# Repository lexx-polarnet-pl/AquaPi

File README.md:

# AquaPi

The aim of this project is to build Raspberry Pi controlled platform for aquarium management.

## Table of contents
* [General info](#general-info)
* [Screenshots](#screenshots)
* [Versions](#Versions)
* [Setup](#setup)
* [Features](#features)
* [Status](#status)
* [Inspiration](#inspiration)
* [Contact](#contact)

## General info
This project is licensed using GPL 2.0 version.
It's combination of hardware layer and software as well.
Structure of directories is following:

* Software - source codes of daemon and php web ui.
* Hardware - all hardware designs (created using KiCad).
* Doc      - place for documentation.

You can like it or not, but software is written (and documentation as well) in Polish language.

## Screenshots

## Versions
* Version 1.0 - still one and only stable version that was released.
* Version 2.0 - aka still in development phase - far more advanced than previous one, but also still not finished (but quite stable).

## Setup
Please see Doc directory if you wish to learn more about setup process.

## Features
List of features ready:
* Heating/cooling tank with different temperature settings between night and day.
* Light control with PWM usage to simulate sunrise/dawn.
* Recording of statistical data collected from sensors into database, and visualization on charts.
* Can be controlled using web browser, both on PC and mobile phone.
* Outputs controlled with timers with 1 second accuracy (nice for DIY feeders or fertilizers).

TODOs for future development:
* still some stuff to do with CO&#8322;.
* and probably more small staff to do.

## Status
Project is: in progress.

## Inspiration
This project was inspired by [Aquamat](https://github.com/musashimm/aquamat). 

## Contact
Created by [lexx](mailto:lexx@polarnet.pl) (https://lexx.polarnet.pl/) - feel free to contact me!
AquaPi is also having its own home page - see https://aquapi.polarnet.pl/

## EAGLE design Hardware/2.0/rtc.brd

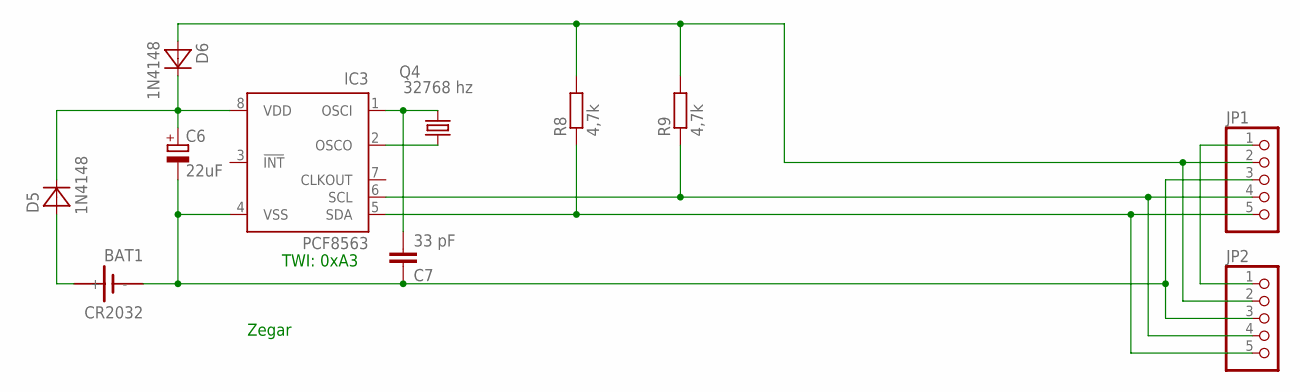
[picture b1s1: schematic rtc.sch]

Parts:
BAT1: CR2032; SN2932_LISPOL
C6: 22uF; E2,5-5
C7: 33 pF; C050-024X044
D5, D6: 1N4148; DO35-7
IC3: PCF8563; DIL08
JP1, JP2: PINHD-1X5/90; 1X05/90
Q4: 32768 hz; TC26V
R8, R9: 4,7k; R1206

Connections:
+5V: D6.A, JP1.2, JP2.2, R8.2, R9.2
+12V: JP1.1, JP2.1
GND: BAT1.-, C6.-, C7.1, IC3.4 (VSS), JP1.3, JP2.3
unnamed: IC3.2 (OSCO), Q4.1
unnamed: C7.2, IC3.1 (OSCI), Q4.2
unnamed: C6.+, D5.C, D6.C, IC3.8 (VDD)
unnamed: BAT1.+, D5.A
SCL: IC3.6 (SCL), JP1.4, JP2.4, R9.1
SDA: IC3.5 (SDA), JP1.5, JP2.5, R8.1

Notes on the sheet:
TWI: 0xA3
Zegar

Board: 2 copper layers, 11 parts (3 on the bottom side), 9 nets, no tracks yet.

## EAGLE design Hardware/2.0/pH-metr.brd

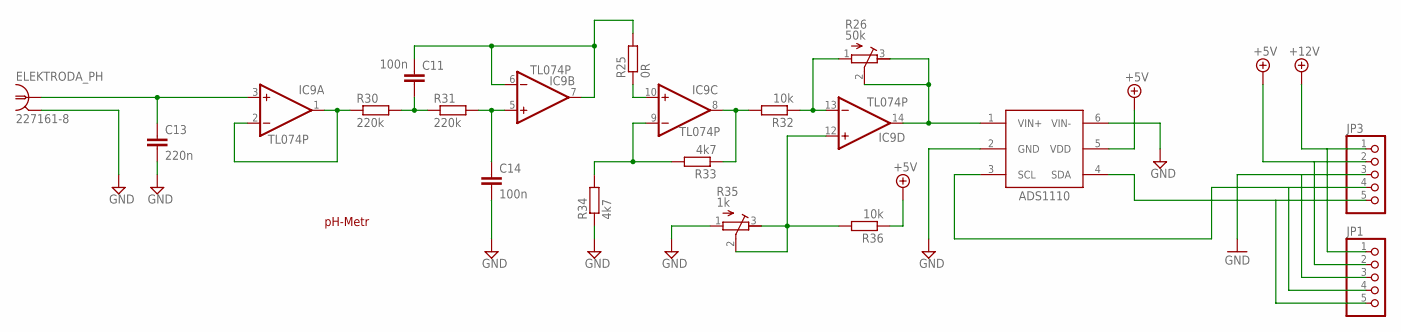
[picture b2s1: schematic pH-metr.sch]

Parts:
C11, C14: 100n; C1206
C13: 220n; C050-025X075
ELEKTRODA_PH: 227161-8; AMP_227161
IC2: ADS1110; SOT-23-6
IC9: TL074P; DIL14
JP1, JP3: PINHD-1X5/90; 1X05/90
R25: 0R; R1206
R26: 50k; RTRIM64X
R30, R31: 220k; R1206
R32, R36: 10k; R1206
R33, R34: 4k7; R1206
R35: 1k; RTRIM64X

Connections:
+5V: IC2.5 (VDD), JP1.2, JP3.2, R36.1
+12V: JP1.1, JP3.1
GND: C13.2, C14.2, ELEKTRODA_PH.2 (GND), IC2.2 (GND), IC2.6 (VIN-), JP1.3, JP3.3, R34.1, R35.1 (A)
unnamed: C13.1, ELEKTRODA_PH.1, IC9.3 (+IN)
unnamed: IC9.12 (+IN), R35.2 (S), R35.3 (E), R36.2
unnamed: IC9.10 (+IN), R25.1
unnamed: IC9.13 (-IN), R26.1 (A), R32.1
unnamed: IC9.1 (OUT), IC9.2 (-IN), R30.1
unnamed: C11.2, R30.2, R31.1
unnamed: C14.1, IC9.5 (+IN), R31.2
unnamed: C11.1, IC9.6 (-IN), IC9.7 (OUT), R25.2
unnamed: IC9.9 (-IN), R33.2, R34.2
unnamed: IC9.8 (OUT), R32.2, R33.1
PHOUT: IC2.1 (VIN+), IC9.14 (OUT), R26.2 (S), R26.3 (E)
SCL: IC2.3 (SCL), JP1.4, JP3.4
SDA: IC2.4 (SDA), JP1.5, JP3.5
V+: IC9.4 (V+)
V-: IC9.11 (V-)

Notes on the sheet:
pH-Metr

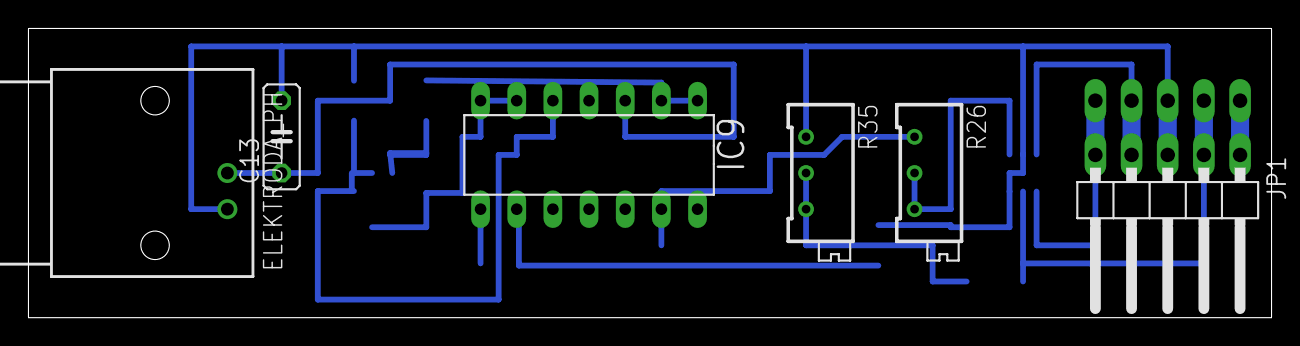
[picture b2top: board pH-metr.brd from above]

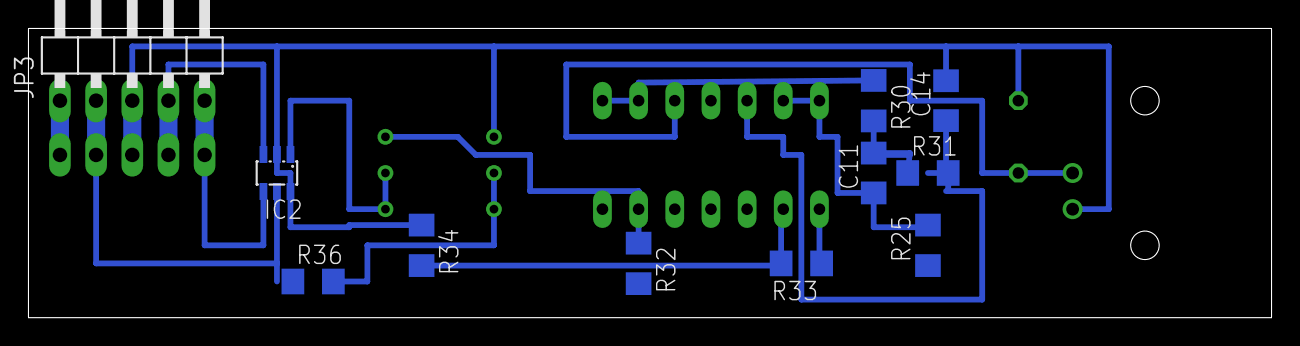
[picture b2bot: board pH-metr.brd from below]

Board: 2 copper layers, 87.3 x 20.3 mm, 17 parts (11 on the bottom side), 16 nets.

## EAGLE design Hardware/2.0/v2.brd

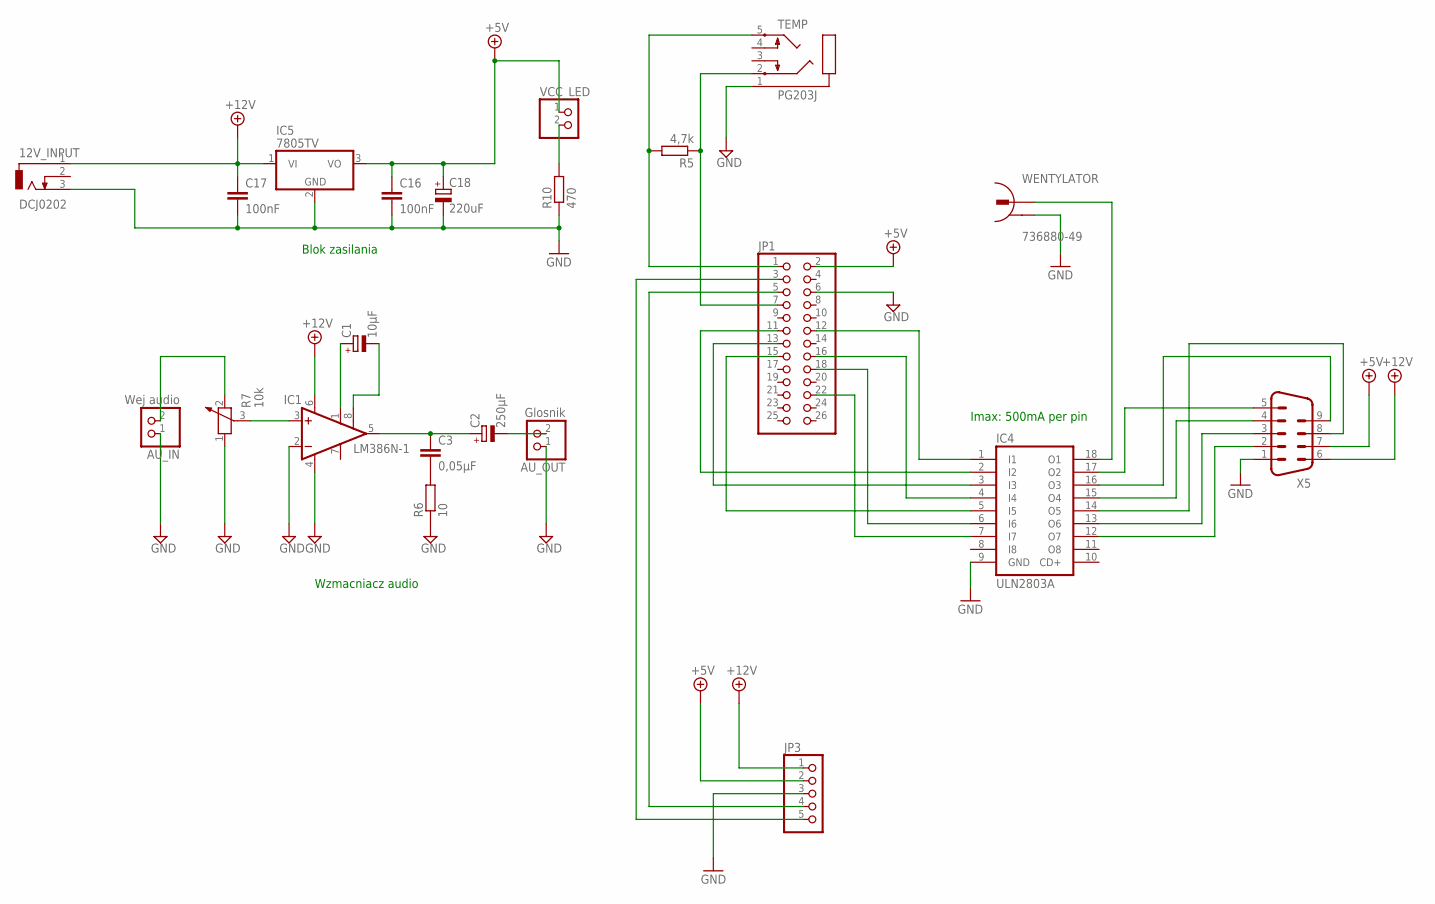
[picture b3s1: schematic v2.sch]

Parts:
12V_INPUT: DCJ0202
AU_IN: Wej audio; 1X02
AU_OUT: Glosnik; 1X02
C1: 10µF; E2,5-5
C2: 250µF; E2,5-6
C3: 0,05µF; C025-024X044
C16, C17: 100nF; C050-024X044
C18: 220uF; E2,5-5
IC1: LM386N-1; DIL08
IC4: ULN2803A; DIL18
IC5: 7805TV; TO220V
JP1: PINHD-2X13; 2X13
JP3: PINHD-1X5/90; 1X05/90
R5: 4,7k; R1206
R6: 10; R1206
R7: 10k; PT-10
R10: 470; R1206
TEMP: PG203J
VCC_LED: PINHD-1X2; 1X02
WENTYLATOR: 736880-49
X5: M09H

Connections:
+5V: C16.1, C18.+, IC5.3 (VO), JP1.2, JP3.2, VCC_LED.1, X5.7
+12V: 12V_INPUT.1, C17.1, IC1.6 (VS), IC5.1 (VI), JP3.1, X5.6
GND: 12V_INPUT.3, AU_IN.1, AU_OUT.1, C16.2, C17.2, C18.-, IC1.2 (-IN), IC1.4 (GND), IC4.9 (GND), IC5.2 (GND), JP1.6, JP3.3, R6.1, R7.1, R10.1, TEMP.1, WENTYLATOR.2, X5.1
unnamed: IC4.3 (I3), JP1.13
unnamed: IC4.4 (I4), JP1.16
unnamed: IC4.1 (I1), JP1.12
unnamed: IC4.13 (O6), X5.3
unnamed: IC4.16 (O3), X5.9
unnamed: IC4.12 (O7), X5.2
unnamed: IC4.7 (I7), JP1.22
unnamed: IC4.5 (I5), JP1.15
unnamed: IC4.14 (O5), X5.8
unnamed: IC4.6 (I6), JP1.18
unnamed: JP1.1, R5.2, TEMP.5
unnamed: JP1.7, R5.1, TEMP.2
unnamed: IC4.17 (O2), X5.5
unnamed: R10.2, VCC_LED.2
unnamed: IC4.18 (O1), WENTYLATOR.1
unnamed: C1.+, IC1.1 (GAIN)
unnamed: IC4.15 (O4), X5.4
unnamed: IC4.2 (I2), JP1.11
unnamed: C1.-, IC1.8 (GAIN)
unnamed: C2.+, C3.1, IC1.5 (OUT)
unnamed: AU_OUT.2, C2.-
unnamed: C3.2, R6.2
unnamed: IC1.3 (+IN), R7.3
unnamed: AU_IN.2, R7.2
SCL: JP1.5, JP3.4
SDA: JP1.3, JP3.5

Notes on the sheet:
Wzmacniacz audio
Blok zasilania
Imax: 500mA per pin

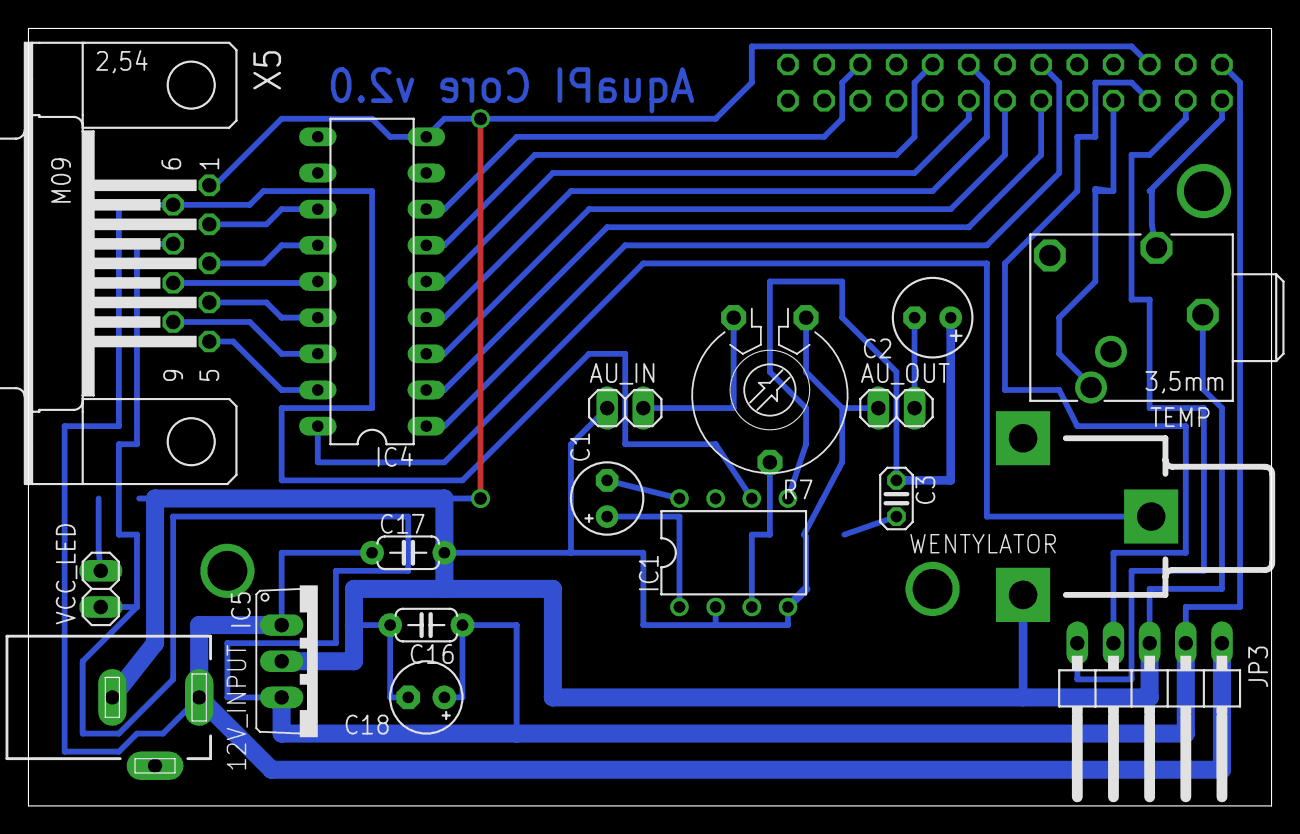
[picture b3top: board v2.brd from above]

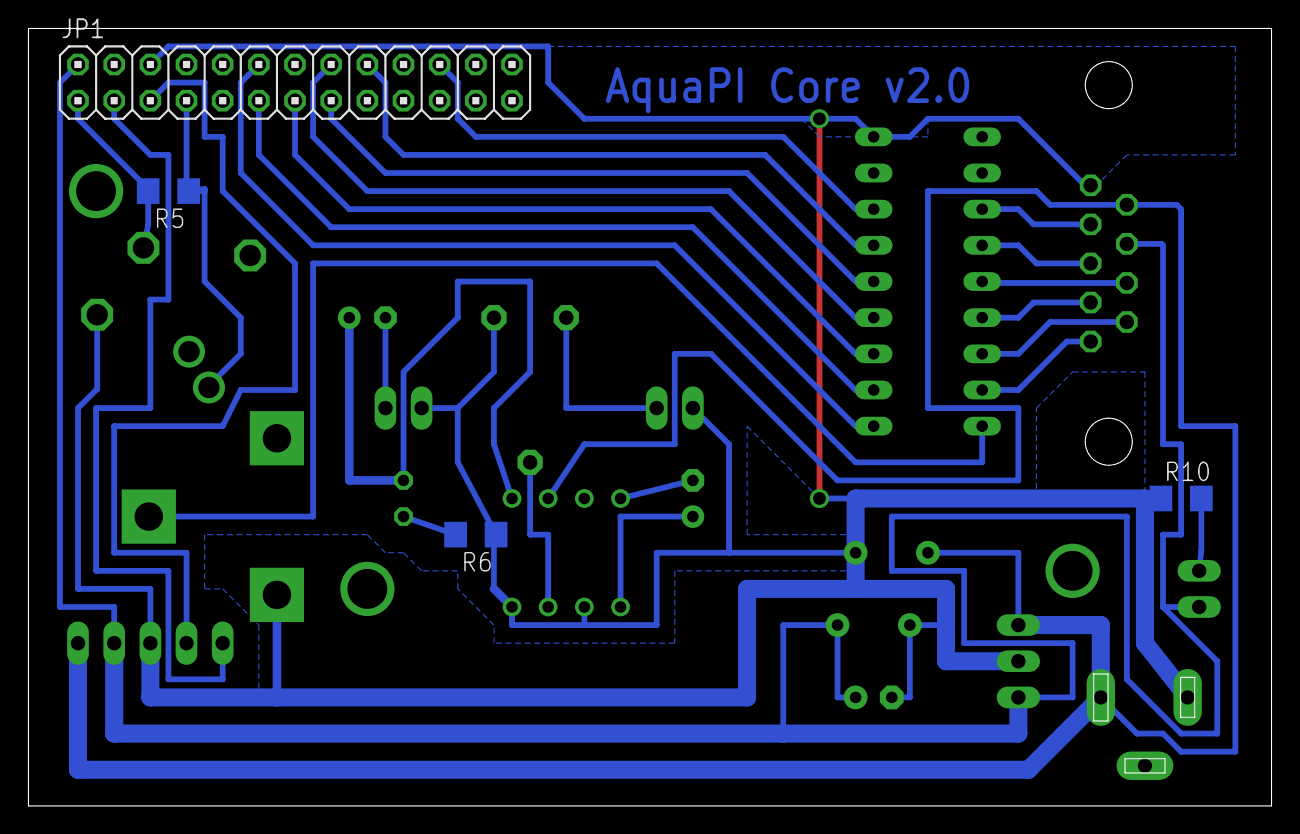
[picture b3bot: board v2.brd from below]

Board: 2 copper layers, 87.3 x 54.6 mm, 22 parts (4 on the bottom side), 29 nets.

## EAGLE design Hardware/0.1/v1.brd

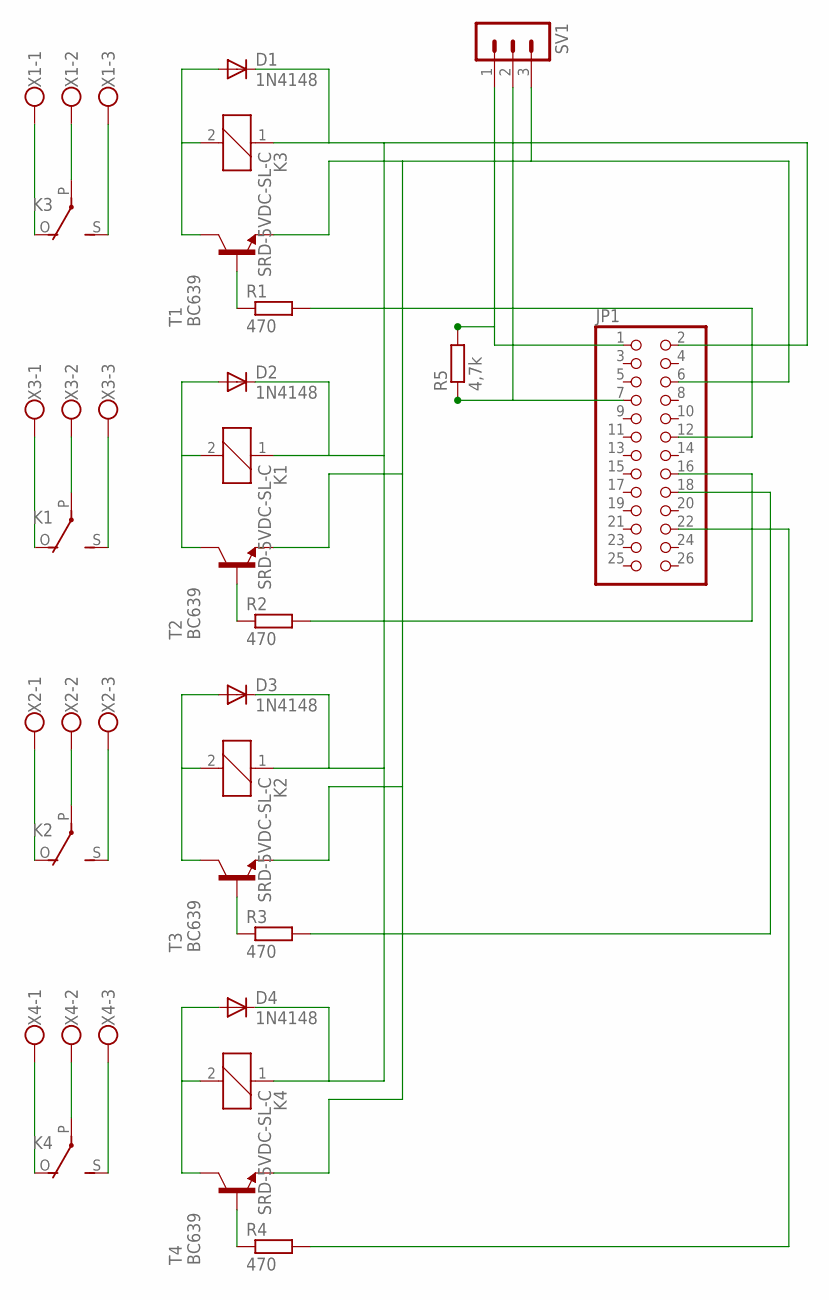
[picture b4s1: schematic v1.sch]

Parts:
D1, D2, D3, D4: 1N4148; DO41-10
JP1: PINHD-2X13; 2X13
K1, K2, K3, K4: SRD-5VDC-SL-C; ZF112
R1, R2, R3, R4: 470; 0204/7
R5: 4,7k; 0207/7
SV1: MA03-1
T1, T2, T3, T4: BC639; TO92-ECB
X1, X2, X3, X4: W237-103

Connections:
unnamed: JP1.12, R1.2
unnamed: D1.A, K3.2, T1.C
unnamed: JP1.16, R2.2
unnamed: JP1.6, SV1.3, T1.E, T2.E, T3.E, T4.E
unnamed: R1.1, T1.B
unnamed: K3.P, X1.2
unnamed: K3.S, X1.3
unnamed: K3.O, X1.1
unnamed: D1.C, D2.C, D3.C, D4.C, JP1.2, K1.1, K2.1, K3.1, K4.1
unnamed: D2.A, K1.2, T2.C
unnamed: JP1.1, R5.2, SV1.1
unnamed: R2.1, T2.B
unnamed: D3.A, K2.2, T3.C
unnamed: K1.P, X3.2
unnamed: K1.S, X3.3
unnamed: K1.O, X3.1
unnamed: R3.1, T3.B
unnamed: JP1.7, R5.1, SV1.2
unnamed: K2.P, X2.2
unnamed: K2.S, X2.3
unnamed: K2.O, X2.1
unnamed: JP1.18, R3.2
unnamed: D4.A, K4.2, T4.C
unnamed: R4.1, T4.B
unnamed: K4.P, X4.2
unnamed: K4.S, X4.3
unnamed: K4.O, X4.1
unnamed: JP1.22, R4.2

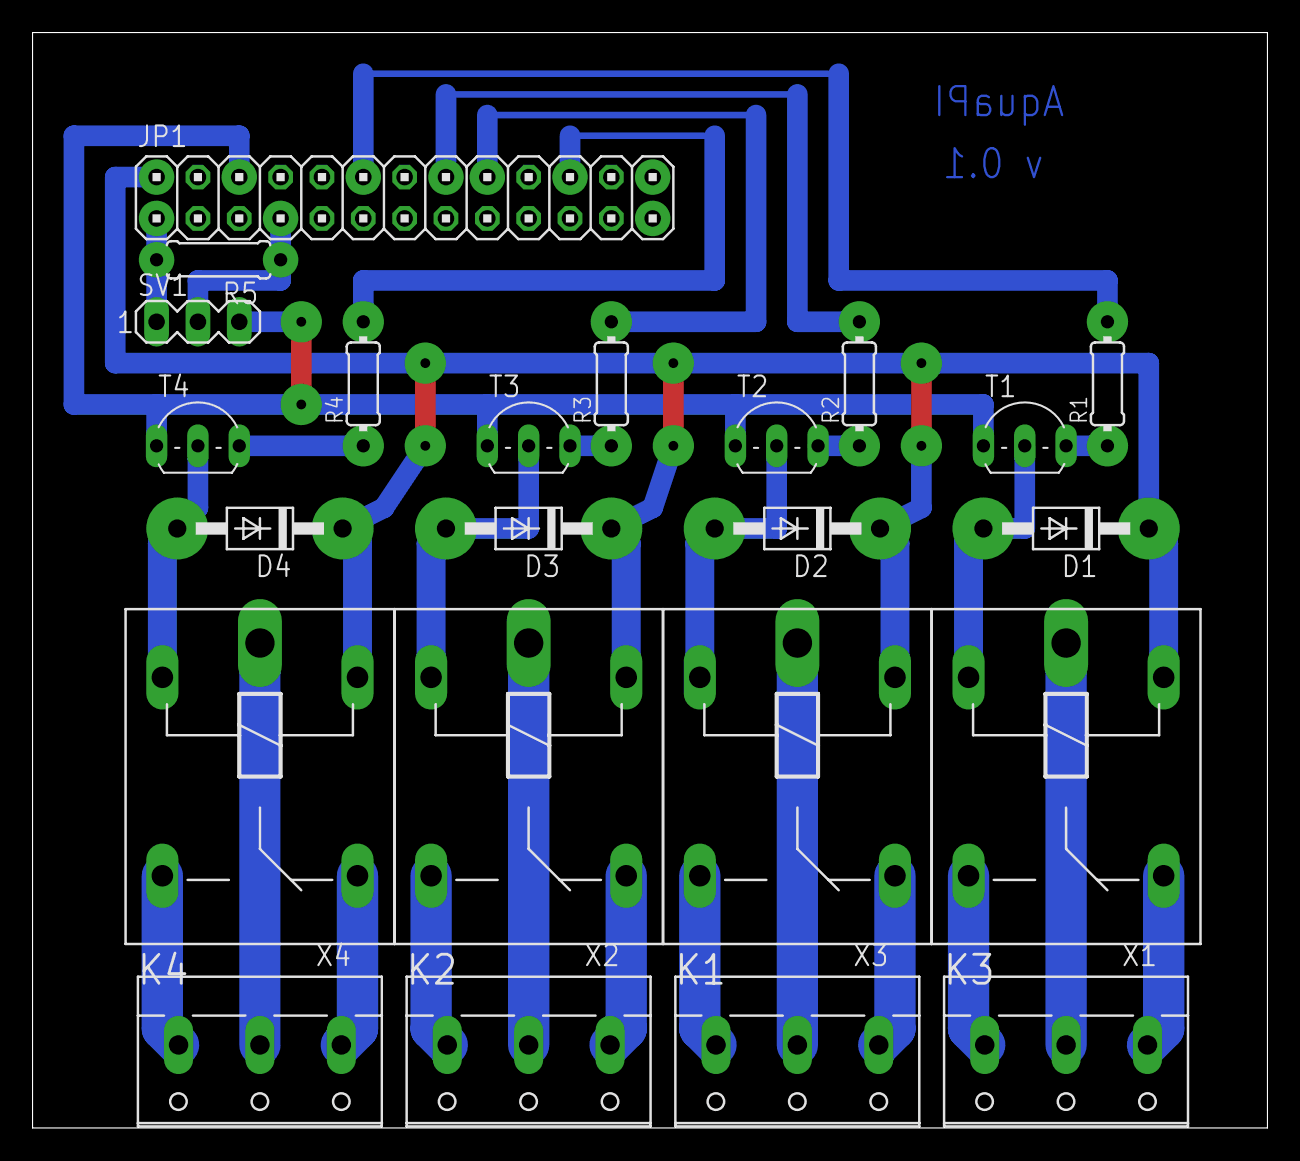
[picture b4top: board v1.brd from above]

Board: 2 copper layers, 75.9 x 67.3 mm, 23 parts (0 on the bottom side), 28 nets.

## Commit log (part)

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2013-11-11 poprawka warunku
2013-11-11 opis
2013-11-11 dostosowanie do nowej klasy DB
2013-11-11 zgodność ze starszą wersja PHP
2013-11-11 mozliwosc nie wyświetlania czujników na wykresie
2013-11-11 implementacja IPC
2013-11-11 Wczytywanie pozostałych parametrów daemona z ini
2013-11-11 poprawki wizualne
2013-11-12 dopasowanie do nowej klasy DB
2013-11-12 Update README.txt
    ort :P
2013-11-13 poprawa formatowania
2013-11-13 dodana lista autorów
2013-11-13 przepis na udaną (prawie) instalację
2013-11-13 fix na pustą baze
2013-11-14 work around na Strict Standards: Only variables should be passed by reference
2013-11-14 poprawka na wypadek braku timerów
2013-11-14 nie mozna było dodac sensora ktory nie miał byc pokazywany na wykresie.
2013-11-14 Update aquapi.sql
    rozszerzenie tabeli sensors
2013-11-14 oznaczanie jednego sensora jako master dla zgodnosci z demonem :(
2013-11-14 zmiana w demonie uwzgledniajaca tabele sensors
2013-11-15 poprawki zwiazane glownie z radzeniem sobie z brakiem danych w bazie
2013-11-15 porządki i zmiana nazewnictwa wyjść
2013-11-15 zapomniany commit
2013-11-16 dodane 2 funkcje pomocnicze
2013-11-16 nowy konfig
2013-11-17 Zaczątki dokumentacji
2013-11-17 przystosowanie strony konfiguracyjnej do nowej bazy + przebudowa
2013-11-18 kolejne poprawki stabilności
2013-11-19 zmiany w dokumentacji
2013-11-19 świerzo wygenerowana dokumentacja
2013-11-19 usunięcie zbędnych fragmentów RelayBoard
2013-11-19 Zmiany w about
2013-11-19 Ujednolicanie WebUi
2013-11-20 sprawdzanie poprawnego odczytu sensorów. błedne odczyty są odrzucane, a zdarzenie logowane
2013-11-20 poprawa drobnych błędów
2013-11-20 poprawki na liczne PHP Notice, poprawka demona, poprawka na brakujący podsystem 1wire.
2013-11-20 memmory leak fix
2013-11-22 2 formatki dodawania timerów.
2013-11-22 poprawka wysypujacego sie demona
2013-11-23 Dodana możliwość zabezpieczenia webui hasłem
2013-11-23 zbędny plik
2013-11-24 demon loguje temperatory z czujnika dummy, poprawka aktualizacji sensorów, temperatury nocne. poprawione duperele.
2013-11-25 ciąg dalszy dokumentacji
2013-11-25 Tu nie jest wymagany
2013-11-25 zmiana
2013-11-26 jeszcze zmiany
2013-11-26 poprawki po merge
2013-12-28 dostosowanie do nowego formatu bazy
2013-12-28 enable $id$ tag
2013-12-29 Podstawowa obsługa timerów (czasowych) jeszcze bez dni tygodnia
2013-12-29 poprawki w UI oraz rozbudowa IPC - statusy urządzeń są teraz czytane bezpośrednio z daemona bez użycia bazy
2013-12-30 konwersja na UTF8
2013-12-30 Raportowanie stanu nieustalonego
2014-01-02 zmiana roku
2014-01-08 Zaczątek obsługi dni tygodnia
2014-01-23 naprawa nie działajacego przełaczania sekcji w ustawieniach
2014-01-24 aktywacja zakładki kamery
2014-01-25 poprawka dashboard o brakujace sekcje. opcja w ini do ich właczania
2014-01-26 Poprawa ustawień czujników, mozliwosc wyłaczenia czujnika, opcja w konfiguracja wskazujaca czy demon jest lokalny czy zdalny, korekta dashboard.
2014-02-02 id + drobne poprawki
2014-02-11 poprawka master sensora
2014-02-13 poprawki czasu, opisów i jakiejs drobnicy.
2014-03-01 Drobna poprawka nagłówka
2014-03-01 Dodany viewport - nie zmniejszaj ekranu na komórkach
2014-03-01 dopiski w dokumentacji
2014-03-01 zwiększenie limitu failcount
2014-03-02 Lekkie poprawki pod urządzenia mobilne, chociaż jeszcze długa droga...
2014-03-02 Eksperyment z layoutem
2014-03-15 poprawka zapisywania nowych sensorów do bazy.
2014-03-15 uruchomienie wykresów. brak wsparcia dla brakujacych danych. (trzeba by generowac null przy wyciaganiu danych)
2014-03-15 poprawka przedrostka dummy
2014-03-15 Update aquapi.c
    literówka
2014-03-15 reload_freq jest obsługiwane
2014-03-15 korekta zapytania
2014-03-16 poprawa wyswietlania logów, czyszczenie logów, nowa opcja w konfigu, zmiana nazwy pliku ini z konfiguracją.
2014-03-16 poprawka na brakujaca opcje aby nie czysciło całych logów
2014-03-16 zmiana ikonek
2014-03-16 Update aquapi.ini
    opcja kamera
2014-03-16 dopasowanie do nowego konfiga
2014-03-16 wyłaczanie kawałków kodu zgodnie z opcjami w ini
2014-03-16 Update tcpip.c
    config.interface => config.host
2014-03-16 Update aquapi.c
    bind-address, bind-port
2014-03-16 Update tcpip.c
    _
2014-03-16 Update aquapi.c
    _
2014-03-16 Update inifile.c
    _
2014-03-16 Update aquapi.ini
    _
2014-03-16 wartości domyślne
2014-03-16 negowanie wyjść
2014-03-16 usunięcie $Id
2014-03-16 dodano xml2array
2014-03-16 Delete aquapi2.ini
    nie potrzebny
2014-03-16 dopasowanie ustawien do ipc->1wlist
2014-03-16 ustandaryzowanie nazwy templatki
2014-03-16 kolorowanie i lepsze opisy dla devel
2014-03-16 fix, ale brzydki
2014-03-17 mozliwosc usuniecia czujników dummy
2014-03-17 poprawka wizualna
2014-03-17 Usunięcie zbędnych $Id$
2014-03-18 lepsza obsługa rb
2014-03-18 usuniecie usera
2014-03-18 usunięcie usera
2014-03-18 obsługa czujników systemowych
2014-03-18 aktualizacja struktury DB
2014-03-18 cleanup i dodanie komendy aquapi:sysinfo
2014-03-18 poprawki
2014-03-19 poprawki konfiguracji gpio, zmina zrodla danych dashboarda
2014-03-19 Dodanie obsługi korekty temp. nocnej
2014-03-19 zapis stanu wyjść
2014-03-19 usunięte już zrobione
2014-03-19 kolejne zrobione
2014-03-19 Wycięcie warningów
2014-03-20 wartości nieokreślone z czujników są zapisywane w bazie jako null
2014-03-21 obsługa wyłaczonych czujników + opis typów wejsc RB
2014-03-21 przeróbka dashboard
2014-03-21 dodana obsługa taga <NOBR></NOBR>
2014-03-22 wykresy przekaźników, wyłaczanie przekaźników w konfiguracji, rożne drobne poprawki.
2014-03-22 porawka tytułu
2014-03-22 fix tabeli
2014-03-22 poprawka Jarka
2014-03-22 początek obsługi manualnego włączania wyjść w demonie
2014-03-31 dodanie obsługi pseudoczujnika rpi:system:txtfile
2014-03-31 poprawka na odczyt 85stopni z DSa
2014-03-31 plugin odczytujacy pogode :)
2014-04-01 dodane identyfikatory sensorów
2014-04-01 dodanie 2 tabeli
    dodanie tabeli jednostek oraz relacji jednostek z interfejsami
2014-04-01 dodanie konfigurowalnych jednostek dla sensorów
2014-04-05 drobne fixy
2014-04-05 poprawka symbolu jednostki
2014-04-06 przeniesienie pluginów
2014-04-06 plugin weather.php uzywa danych z pliku ini i bazy.
2014-04-06 poprawka pluginu
2014-04-06 https://github.com/lexx-polarnet-pl/AquaPi/issues/21
    sensor głowny wyswietla sie na dashboard
2014-04-06 pwm w UI
2014-04-06 trigery pwm w UI
2014-06-16 Update aquapi.sql
    dodanie nowej tabeli
2014-06-16 zmiana sposobu kasowania
2014-06-29 poprawka zapisywania kalendarza. sekcja ustawienien urzadzenia wyswietla sie na podstawie właczonego/wyłaczonego urzadzenia, a nie na podstawie istnienia interfejsów tego urzadzenia.
2014-06-29 zmiana sposobu prezentacji timestampów
2014-06-29 dodanie kalendarza i jego obsługi
2014-06-29 Update aquapi.sql
    db_version fix
2014-06-30 poprawka na dirty hack
2014-07-01 poprawa zdarzen z kalendarza na dashboardzie
2014-07-02 zapomniany plik z upgradem
2014-07-02 kolorowanie komunikatów z kalendarz, odczyt s/n płyty rpi.
2014-07-02 dodanie opcji właczania i wyłaczania nowych sekcji/pluginów
2014-07-04 mod bazy pod zatwierdzanie zdarzeń
2014-07-04 to też powinno być opcjonalne
2014-07-05 dodany tip
2014-07-05 demon nie powinien się wywalać na systemach innych niż raspi przy próbie użycia GPIO
2014-07-06 na -O3 segfaulci na i386, piwo temu kto mi powie czemu
2014-07-06 zmniejszenie czasu oczekiwania na zmianę stanu interfacu + poprawa obsługi w UI
2014-07-06 poprawka formatu daty na bardziej czytelną
2014-07-07 usunięte zbędne dzielenie
2014-07-07 wizualizacja trybu auto i ręcznego
2014-07-07 Pokazywanie wszystkich wyjść w jednej tabelce
2014-07-08 negowanie
2014-07-08 negowanie było w złym miejscu
2014-07-09 todo jest teraz wissues na githubie
2014-07-13 podejście do tematu jak wyświetlać możliwe do ustawienia wejścia/wyjścia
2014-07-21 nieco inne dodawanie urządzeń
2014-07-22 poprawka na wejścia fully_editable_address (czyli np. plik tekstowy)
2014-08-01 Dodana (wstępna bo czekam na sondę) obsługa modułu miniPh (pomiar pH) oraz wyczyszczenie i poprawa obsługi expanderów i2c opartych o pcf8574
2014-08-01 Poprawki w obsłudze i2c
2014-08-01 wzmianka o i2c
2014-08-01 Przekompilowana dokumentacja
2014-08-01 Jak doprecyzować o co pytamy
2014-08-02 Przepisana reszta na libxml
2014-08-03 Teraz porty GPIO też mogą być wejściami
2014-08-03 demon mówi że GPIO może być też input
2014-12-27 Test nowego podejścia
2015-01-04 Kolejne dodatki
2015-01-05 początki zapisów do bazy
2015-01-06 ciąg dalszy prac
2018-04-06 zmiany w statystykach
2018-04-07 charts cleanup
2018-04-07 poprawki w CSS
2018-04-10 zmiana ilości logów z 30 na 100 jednocześnie na ekranie
2018-04-10 zaczątek możliwoścu ustawiania koloru przy interface
2018-04-13 nowe ikonki i zmiany w listach
2018-04-13 kolor wykresu zależy od ustawień w bazie
2018-06-05 robi się ładniej i ładniej
2018-12-02 ostatnie zmiany, głównie przejście z mysql na mysqli
2018-12-03 zmiany w pwm
2018-12-03 jeszcze kilka zmian w pwm
2018-12-07 kasacje
2018-12-08 czyszczenie kodu + przywrocenie niektorych plikow
2018-12-09 nie pokazuj bledow
2018-12-15 zmiany w timerach i ikonkach
2018-12-23 kolejne zmiany w ui + wsparcie dla jednostek
2019-01-01 poprawiona paginacja
2019-12-27 nowe readme
2019-12-27 zmiana układu na dashboard
2019-12-28 poprawka w jednostkach i odswierzanie ajax co 1 sec
2019-12-28 poprawiona konwersja liczb oraz odświerzanie co sekundę
2019-12-29 drobne zmiany
2019-12-30 dodanie funkcjonalności nawożenia co2 oraz kalibrowania sondy pH
2019-12-31 nowy screanshot
2019-12-31 ikonki przy urządzeniu są teraz we wszystkich menu
2020-01-02 dodanie opisu podłączenia urządzeń w dokumentacji
2020-01-02 dodany link do strony domowej aquapi
2020-01-05 czyszczenie kodu
2020-01-05 dalsze czyszczenie kodu
2020-01-06 nowy zrzut sql z aktualną strukturą bazy
2020-01-06 dalsze czyszczenie kodu i optymalizacja danych debug
2020-01-06 aktualizacja aquapi.ini do aktualnych danych
2020-01-06 drobne zmiany pod nowe raspi
2020-01-06 aktualizacja rozdzialu o instalacji aquapi
2020-01-13 zmiany w obsłudze mostka
2020-01-15 żegnamy brzydkie delay, witamy wywołanie sygnału co sekundę jako alarm
2020-02-24 kolejne zmiany w co2 (histereza)
2020-02-24 parametry wody
2020-02-25 wracamy do loop i delaj, sygnały nie wypaliły?
2020-02-28 poprawka w zapisywaniu statystyk
2020-02-29 dodanie opcji konfiguacji histerezy przy nawożeniu co2
2020-02-29 poprawa liczenia średniej pomiarów z sondy pH
2020-02-29 sysinfo jest odświerzane ajaxem
2020-03-01 poprawki w sterowaniu co2
2020-03-01 dodany scenariusz zachowania na wypadek awarii czujników
2020-03-01 nowa ikonka
2020-03-07 zmiana w pokazywaniu kolejności urządzeń na ekranie konfiguracji
2020-03-07 poprawki w ajax refresh
2020-04-19 nowsza wersja wiringpi
2020-04-19 przymiarki do obsługi ads1115
2020-04-20 dalsze zmiany
2020-04-20 zapomniany dwukropek
2020-04-20 zmiana w nazewnictwie pinów mostka ADC
2020-04-20 nowe jednostki
2020-04-25 literówki (poprawka)
2020-04-25 dodanie ADS1115 do dokumentacji
2020-05-01 skasowanie starych wersji płytek
2020-05-01 nowa płyta główna
2020-05-01 Poprawki w płycie głównej
2020-05-03 ominięcie problemu wyświetlania surowych wartości na UI przy pH
2020-06-14 nowy projekt sprzętu
2020-06-18 wielopoziomowe menu
2020-06-19 Skasowanie alarmów z modułu temp, i zrobienie alarmów uniwersalnych, możliwych do ustawienia dla każdego wejścia
2020-06-20 dwie nowe tabele
2020-06-20 dodanie notyfikacji na maila
2020-06-20 drobne zmiany w dokumentacji
2020-06-21 notyfikacje generują się nie częściej niż co 10 min, zapobiega "zalewaniu" błędami logów
2020-06-25 znowu można wybrać sondę co2
2020-07-01 poprawka wizualna wykresu kalibracyjnego
2021-12-30 jack 3,2 a nie 2,5
2022-01-06 Dodana obsługa pca9685
2022-01-06 Dodane zdjęcia zlożonego PWM board
2022-01-06 ignore .htaccess
2022-01-06 aktualizacja chart.js
